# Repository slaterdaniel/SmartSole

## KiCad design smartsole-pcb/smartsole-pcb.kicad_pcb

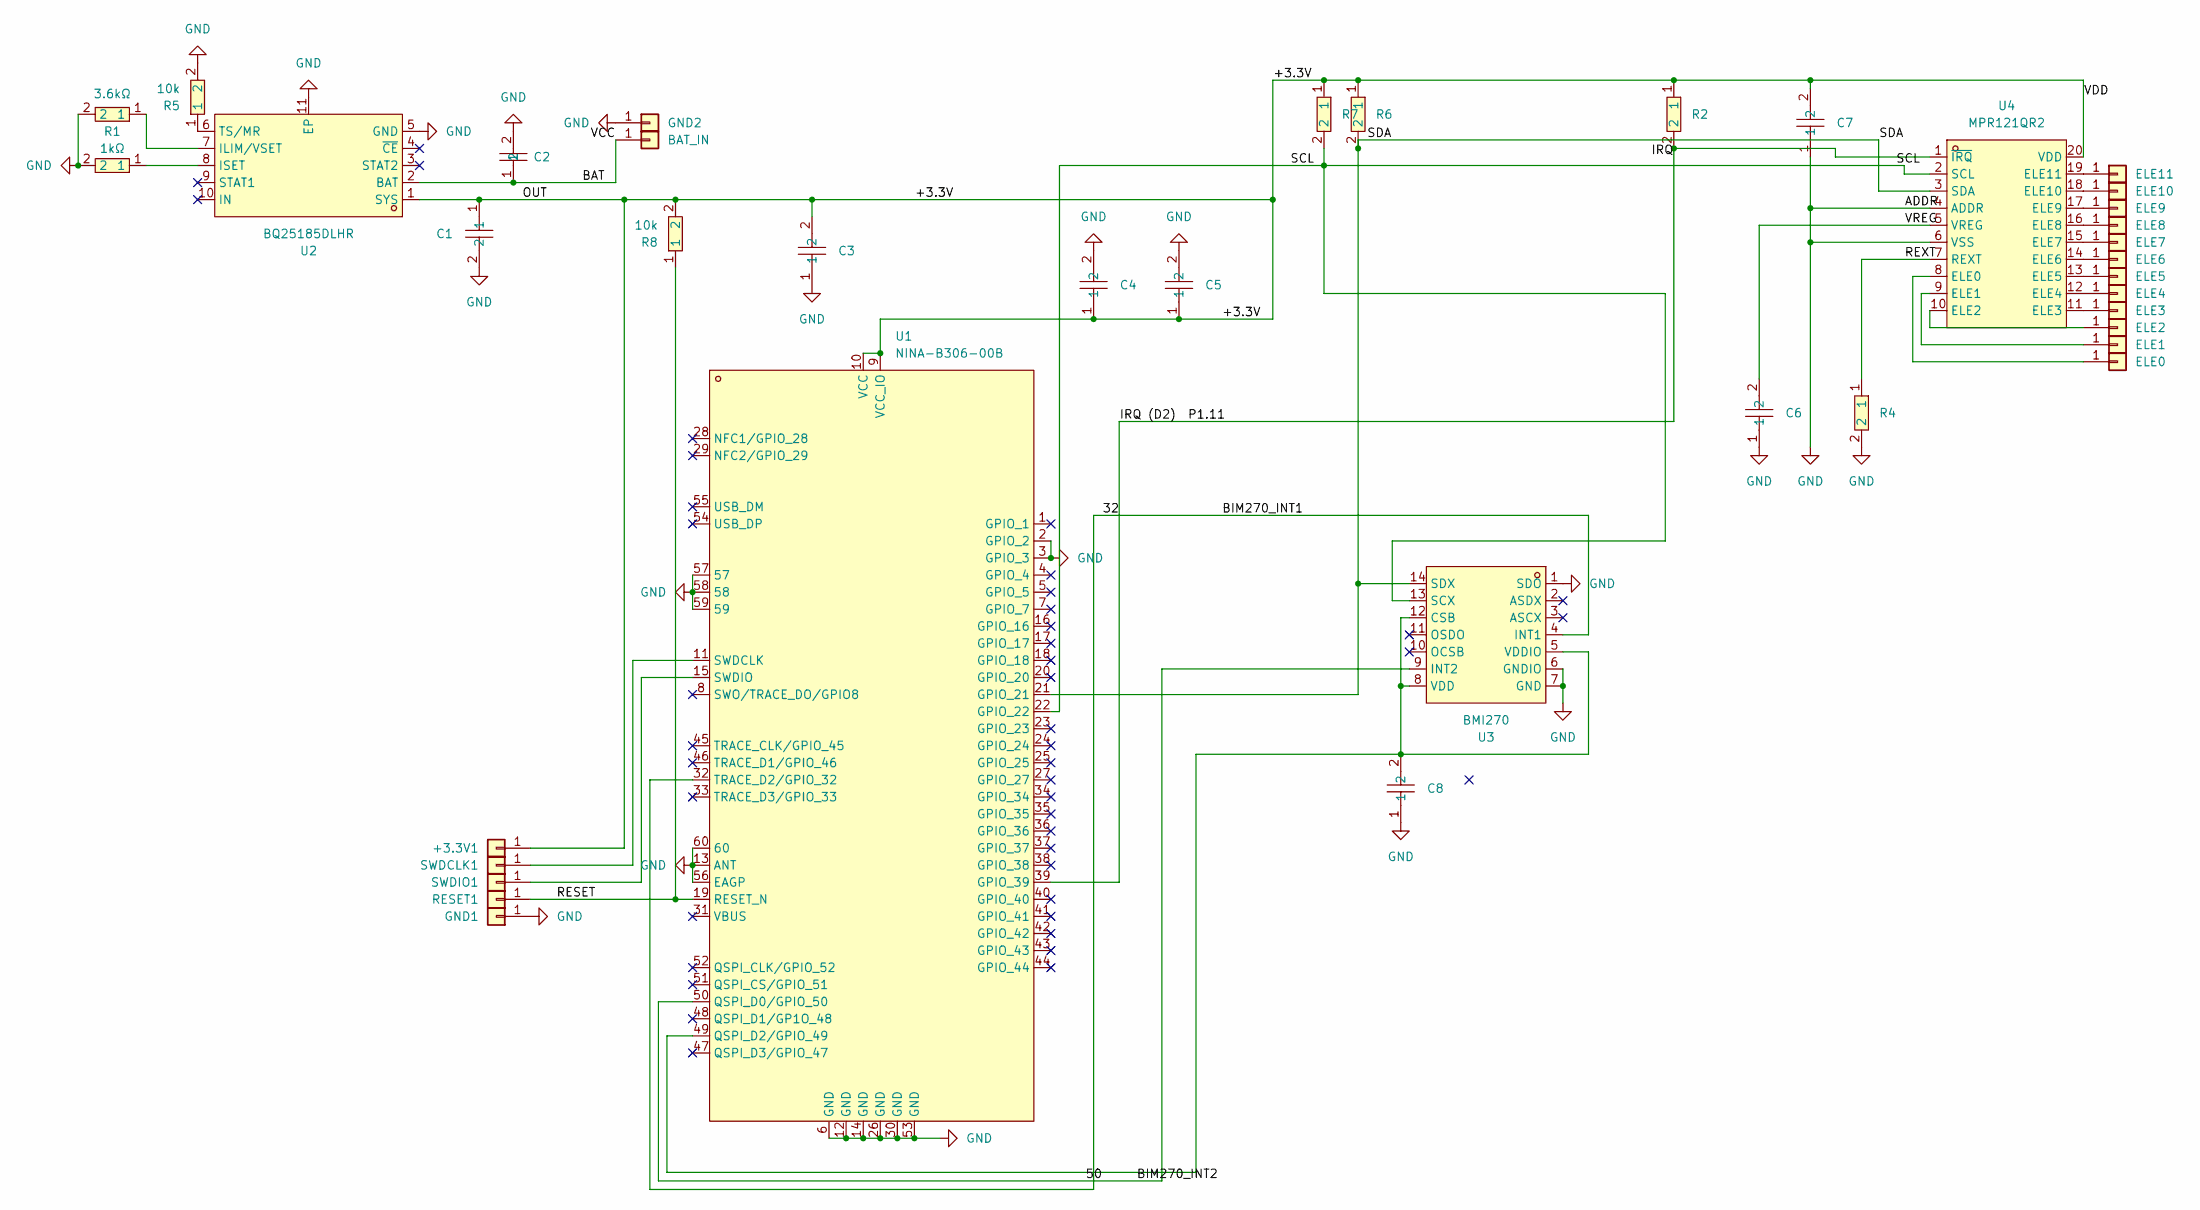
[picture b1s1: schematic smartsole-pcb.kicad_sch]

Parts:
+3.3V1: Conn_01x01; TestPoint_THTPad_1.0x1.0mm_Drill0.5mm
BAT_IN: Conn_01x01; TestPoint_THTPad_1.0x1.0mm_Drill0.5mm
C1: CL10A106MQ8NNNC; C0603; MPN CL10A106MQ8NNNC; LCSC Part C1691
C2: CL10A105KO8NNNC; C0603; MPN CL10A105KO8NNNC; LCSC Part C1592
C3, C4, C5, C6, C7, C8: CT41G-0805-2X1-50V-0.1μF-M; C0805; MPN CT41G-0805-2X1-50V-0.1uF-M(N); LCSC Part C138340
ELE0, ELE1, ELE2, ELE3, ELE4, ELE5, ELE6, ELE7, ELE8, ELE9, ELE10, ELE11: Conn_01x01; TestPoint_THTPad_1.0x1.0mm_Drill0.5mm
GND1, GND2: Conn_01x01; TestPoint_THTPad_1.0x1.0mm_Drill0.5mm
R1: 3.6kΩ; R0603; MPN 0603WAF3601T5E; LCSC Part C22980
R2, R6, R7: 0805W8F4701T5E; R0805; MPN 0805W8F4701T5E; LCSC Part C17673
R3: 1kΩ; R0603; MPN RC0603JR-071KL; LCSC Part C14676
R4: 0805W8F7502T5E; R0805; MPN 0805W8F7502T5E; LCSC Part C17819
R5, R8: 10k; R0805; MPN 0805W8J0103T5E; LCSC Part C25612
RESET1: Conn_01x01; TestPoint_THTPad_1.0x1.0mm_Drill0.5mm
SWDCLK1: Conn_01x01; TestPoint_THTPad_1.0x1.0mm_Drill0.5mm
SWDIO1: Conn_01x01; TestPoint_THTPad_1.0x1.0mm_Drill0.5mm
U1: NINA-B306-00B; LGA-60_L15.0-W10.0-NINA-B406-00B; MPN NINA-B306-00B; LCSC Part C6127317
U2: BQ25185DLHR; WSON-10_L2.2-W2.0-P0.40-BL-EP_TI_DLH0010A; MPN BQ25185DLHR; LCSC Part C19725033
U3: BMI270; LGA-14_L3.0-W2.5-P0.50-BR; MPN BMI270; LCSC Part C2836813
U4: MPR121QR2; QFN-20_L3.0-W3.0-P0.40-BL; MPN MPR121QR2; LCSC Part C91322

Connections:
/32: U1.32 (TRACE_D2/GPIO_32), U3.4 (INT1)
/50: U1.50 (QSPI_D0/GPIO_50), U3.9 (INT2)
/+3.3V: +3.3V1.1 (Pin_1_1), C1.1, C3.2, C4.1, C5.1, C7.2, R2.1, R6.1, R7.1, R8.2, U1.9 (VCC_IO), U1.10 (VCC), U2.1 (SYS), U4.20 (VDD)
/BAT: BAT_IN.1, C2.1, U2.2 (BAT); also elsewhere on the board
/IRQ: R2.2, U1.39 (GPIO_39), U4.1 (~IRQ)
/RESET: R8.1, RESET1.1 (Pin_1_1), U1.19 (RESET_N)
/REXT: R4.1, U4.7 (REXT)
/SCL: R7.2, U1.22 (GPIO_22), U3.13 (SCX), U4.2 (SCL)
/SDA: R6.2, U1.21 (GPIO_21), U3.14 (SDX), U4.3 (SDA)
/VREG: C6.2, U4.5 (VREG)
GND: C1.2, C2.2, C3.1, C4.2, C5.2, C6.1, C7.1, C8.1, GND1.1 (Pin_1_1), GND2.1 (Pin_1_1), R1.2, R3.2, R4.2, R5.2, U1.2 (GPIO_2), U1.3 (GPIO_3), U1.6 (GND), U1.12 (GND), U1.13 (ANT), U1.14 (GND), U1.26 (GND), U1.30 (GND), U1.53 (GND), U1.56 (EAGP), U1.57, U1.58, U1.59, U1.60, U2.5 (GND), U2.11 (EP), U3.1 (SDO), U3.6 (GNDIO), U3.7 (GND), U4.4 (ADDR), U4.6 (VSS)
unnamed: ELE0.1 (Pin_1_1), U4.8 (ELE0)
unnamed: ELE1.1 (Pin_1_1), U4.9 (ELE1)
unnamed: ELE2.1 (Pin_1_1), U4.10 (ELE2)
unnamed: ELE3.1 (Pin_1_1), U4.11 (ELE3)
unnamed: ELE4.1 (Pin_1_1), U4.12 (ELE4)
unnamed: ELE5.1 (Pin_1_1), U4.13 (ELE5)
unnamed: ELE6.1 (Pin_1_1), U4.14 (ELE6)
unnamed: ELE7.1 (Pin_1_1), U4.15 (ELE7)
unnamed: ELE8.1 (Pin_1_1), U4.16 (ELE8)
unnamed: ELE9.1 (Pin_1_1), U4.17 (ELE9)
unnamed: ELE10.1 (Pin_1_1), U4.18 (ELE10)
unnamed: ELE11.1 (Pin_1_1), U4.19 (ELE11)
unnamed: SWDCLK1.1 (Pin_1_1), U1.11 (SWDCLK)
unnamed: SWDIO1.1 (Pin_1_1), U1.15 (SWDIO)
unnamed: C8.2, U1.49 (QSPI_D2/GPIO_49), U3.5 (VDDIO), U3.8 (VDD), U3.12 (CSB)
unnamed: R1.1, U2.7 (ILIM/VSET)
unnamed: R3.1, U2.8 (ISET)
unnamed: R5.1, U2.6 (TS/MR)

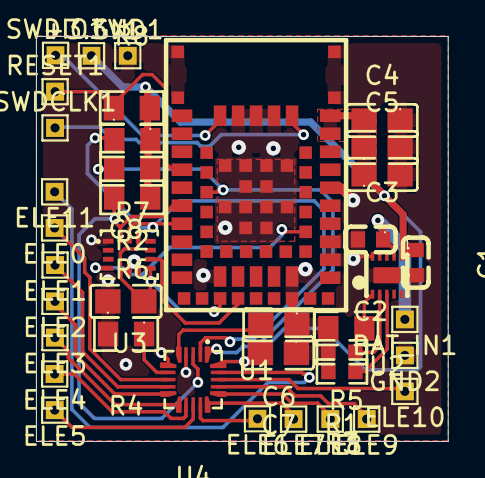
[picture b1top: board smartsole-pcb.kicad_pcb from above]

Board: 2 copper layers, 22.9 x 22.5 mm, 39 parts (0 on the bottom side), 29 nets.

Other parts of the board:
BAT_IN1: Conn_01x01; TestPoint_THTPad_1.0x1.0mm_Drill0.5mm

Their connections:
/BAT: BAT_IN1.1 (Pin_1_1); also elsewhere on the board

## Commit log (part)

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2026-06-08 created homepage, app icon, ble scanner, ble connection
2026-06-08 clear unneed images, add comments for clarity, establish peripheral service readings
2026-06-08 created filtered SmartSole Device Scanning and multi device selection
2026-06-09 drafted data display page
2026-06-09 implemented session settings page
2026-06-09 cleaned up AlllDeviceScanner navigation
2026-06-09 match device family finder with session settings page
2026-06-09 add AllDeviceScanner to Hompage as a button
2026-06-09 added darkmode/lightmode color scheme capabilities for connected Devices List background
2026-06-09 WaitingForRep page stylized
2026-06-09 uniform text coloring for found Device List
2026-06-09 remove unnecesary testing files
2026-06-09 initia commit of arduino .ino files
2026-06-09 restructure repo for clarity
2026-06-09 attempt to restructure to allow for pull request
2026-06-10 remove uneeded Combine import
2026-06-10 establish basic peripheral services and characteristics (data, battery)
2026-06-10 allow for multi device connection
2026-06-10 cleanup navigation to avoid nested NavigationStacks
2026-06-11 re structure .ino files for clarity
2026-06-11 implemented accelrometer_test.ino
2026-06-11 insole .ino file implemented
2026-06-11 consolidate accelerometer axis values
2026-06-11 gyroscope_test.ino implemented
2026-06-11 added angles calculations to accelerometer test
2026-06-11 added angle acceleration characteristic.
    integrated angle, acceleration, and angle acceleration to data.
2026-06-12 setup rep listener framework (without force sensor logic)
2026-06-12 CAD and print Honeycomb V1 - V3
2026-06-13 renamed scanner to manager and outlined characteristic handling
2026-06-13 rename ble scanner to ble manager
2026-06-13 fixed characteristic adding to services
2026-06-13 adjust charateristic types
2026-06-13 remove uneeded Started notification handler
2026-06-14 reduce characteristics to one for reliability
2026-06-14 implemented environment object instead of passing blemanager as parameter
2026-06-16 CAD and print Honeycomb test pads V2.1 and V3.1
2026-06-16 implement madgwick filter for angles
2026-06-16 add 3D shoe models for RealityKit live simulation
2026-06-16 remove breakpoint
2026-06-16 project dev cleanup
2026-06-16 implement code for live 3D simulation with RealityKit
2026-06-21 drafted 12 electrode force sensor code
2026-06-22 updated force_sensor prototype to account for 12 electrodes
2026-06-22 added python matplotib script for heatmap of force sensing
2026-06-25 3D Shoe Model: pivot to using quaternions with euler angle adjustments
2026-06-27 adjust mpr121 constants
2026-06-27 add pattern recognition to force sensor testing
2026-06-27 implemented force sensing to main insole code
2026-06-27 renamed runData struct to RunData
2026-06-27 swift cleanup
2026-06-27 added seperate file for nano builtin utilities
2026-06-27 fixed nano testing variable types
2026-06-27 removed uneeded touch status check
2026-06-28 mpr121 speed testing
2026-06-28 adjust app to match imu output
2026-06-28 access readings through direct i2c registers for speed
2026-06-28 add comments for clarity
2026-06-28 migrated pattern recognition to allow for model display in app prior to rep starting
2026-06-28 moved all app files into seperate folder
2026-06-30 replace hardcoded constants with elements from Constants.h
